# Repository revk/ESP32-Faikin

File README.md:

### Name change

Yes, it seems Daikin don't like Faikin, and I don't have the time or money to argue.

# ESP32-Faikout

Everyone knows Daikin make some of the best air conditioners out there, mechanically speaking. Sadly their WiFi control modules are not so good, especially the latest models which are all cloud based, require an internet connection to even work, and are slow.

This code/module provides local control via web interface, MQTT, and HomeAssistant integration, all with no cloud crap.

* There is also a new [Faikout Remote Control](https://remote.revk.uk/) available, BLE linked to the Faikout, with environmental sensors, available on Tindie now.

PCB designs are included, and also available to buy on [Tindie](https://www.tindie.com/stores/revk/), and on [Amazon UK](https://www.amazon.co.uk/dp/B0G1TP8XCQ). There are other people making and selling, e.g. on [eBay Australia](https://www.ebay.com.au/itm/186860658654).

I'd like to thank the contributors, but contributions are made and accepted on basis that you issue your contribution under the same GPL licence as the project. Forks are allowed on the basis that your forks are on the same GPL licence as the project.

## Trademark

This is an open source project, but bear in mind you cannot sell boards bearing the Andrews & Arnold Ltd name, the A&A logo, the registered trademark AJK logo, or the GS1 allocated EANs assigned to Andrews & Arnold Ltd.

## Further manuals / links

- [Work in progress / release notes](https://github.com/revk/ESP32-Faikout/wiki/Work-in-progress)
- [Wiring](https://github.com/revk/ESP32-Faikout/wiki/Wiring)
- [Setup](Manuals/Setup.md) Manual
- [Controls](Manuals/Controls.md) Manual
- [Advanced](Manuals/Advanced.md) Manual
- [ESP8266 port](https://github.com/Sonic-Amiga/ESP8266-Faikin) of this code
- [list of supported air-con](https://github.com/revk/ESP32-Faikout/wiki/List-of-confirmed-working-air-con-units) WiKi (please update as needed)
- [DoC](Manuals/DoC.md) and Vulnerability disclosure policy
- [S21](Manuals/S21.md) reverse engineered details of `S21` protocol

For support, see issues and discussions.

## PCB and case

The boards from [Tindie](https://www.tindie.com/stores/revk/), [eBay](https://www.ebay.com.au/itm/186860658654), and [Amazon UK](https://www.amazon.co.uk/dp/B0G1TP8XCQ) works with Daikin modules via an `S21` connector, or `X50A` and `X35A` connectors, or similar. The design is updated from time to time so may not look exactly like this.

The case design matches the PCB (check dates match). Designed for resin printing.

Supplied in a 70x70 panel as an assembled PCB with snap off parts down to two sizes. 45x36mm or 40x16mm.

## Why I made this

The history is that, after years of using Daikin air-con in my old home, and using the local http control, in my new house in Wales the WiFi was all cloud based with no local control, and useless, and slow. Just configuring it was a nightmare. I spent all day reverse engineering it and making a new module to provide local control. Pull requests and feature ideas welcome.

This whole project is almost entirely by me, but with some valuable contributions from others (thank you). All of my bits are copyright by me and Andrews & Arnold Ltd who sponsor the whole project, and released under GPL. Whilst not required by the licence, attribution and links would be appreciated if you reuse this.

## How to get one

As mentioned, [Tindie](https://www.tindie.com/stores/revk/), [eBay](https://www.ebay.com.au/itm/186860658654), and [Amazon UK](https://www.amazon.co.uk/dp/B0G1TP8XCQ).

But also, the PCB designs are published, including production files for [JLCPCB](https://jlcpcb.com). You need to remove trademarks, etc, and you would also need something to program them (TC2030 lead). Obviously you need some experience with PCB ordering and diagnostics if getting your own boards made.

# Set-up

Appears as access point with simple web page to set up on local WiFI. On iPhone the setup page auto-loads.

# Operation

Local interactive web control page using *hostname*.local, no app required, no external internet required.

- [Setup](Manuals/Setup.md) Manual
- [Controls](Manuals/Controls.md) Manual
- [Advanced](Manuals/Advanced.md) Manual

# Design

* KiCad PCB designs included, with JLCPCB production files
* 3D printed case STL files
* Documentation of reverse engineered protocol included

Basically, Daikin have gone all cloudy with the latest WiFi controllers. This module is designed to provide an alternative.

* Simple local web based control with live websocket status, easy to save as desktop icon on a mobile phone
* MQTT reporting and controls
* Works with Home Assistant over MQTT - note Home Assistant can work with HomeKit
* Includes linux mysql/mariadb based logging and graphing tools
* Works with [EnvMon](https://github.com/revk/ESP32-EnvMon) Environmental Monitor for finer control and status display
* or, works with BlueCoinT and Telink [BLE temperature sensor](Manuals/BLE.md) as a remote reference in an auto mode
* Automatically works out if S21 or X50 protocol (used on bigger/ducted units)
* Backwards compatible direct `/aircon/...` URLs

# Building code yourself

Git clone this `--recursive` to get all the submodules, and it should build with just `make`. There are make targets for other variations, but this hardware is the `make pico` or `make s3` version. The `make` actually runs the normal `idf.py` to build which then uses cmake. `make menuconfig` can be used to fine tune the settings, but the defaults should be mostly sane. `make flash` should work to program. If flashing yourself, you will need a programming lead, e.g. [Tazmotizer](https://github.com/revk/Shelly-Tasmotizer-PCB) or similar, and of course the full ESP IDF environment. The latest boards also have 4 pads for direct USB connection to flash with no adaptor. The modules on Amazon come pre-loaded and can upgrade over the air.

The code is normally set up to automatically upgrade the software, checking roughtly once a week. You can change this in settings via MQTT.

If you build yourself, you either need no code signing, or your own signing key. This will break auto-updates which try to load my code releases, so you need to adjuist settings `otahost` and `otaauto` accordingly. You can set these in the build config, along with WiFi settings, etc.

If you want to purchase a pre-loaded assembled PCB, see [Tindie](https://www.tindie.com/stores/revk/), and [Amazon UK](https://www.amazon.co.uk/dp/B0C2ZYXNYQ).

## Flashing code

You will need to connect a suitable programming lead. Boards have a header for USB. The very latest design (expected on Amazon around Sep 2024) has a tag-connect compatible header for a [TC2030-USB-NL](https://www.tag-connect.com/product/tc2030-usb-nl) lead. Note that the latest boards have testr pads on the back which include USB, so you can solder a USB lead if necessary.

See [https://github.com/revk/ESP32-RevK](https://github.com/revk/ESP32-RevK) for more details of how to flash the files easily.

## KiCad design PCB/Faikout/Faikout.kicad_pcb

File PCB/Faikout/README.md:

# Faikout

## Trademark

This is an open source project, but bear in mind you cannot sell boards or cases bearing the Andrews & Arnold Ltd name, the A&A logo, the registered trademark AJK logo, or the GS1 allocated EANs assigned to Andrews & Arnold Ltd.

## PCB Designs

These files are for use with [KiCAD](https://www.kicad.org).

- [Faikout](Faikout.kicad_pro)

## 3D

3D case designs are normally automatically created from the PCB so as to ensure correct details and placement of apertures, etc.

|Design|Bottom|Top|Combined|
|------|------|---|--------|
|Faikout||||

## PCB Images

---

*Auto generated README.md 2025-11-12T08:11:45*

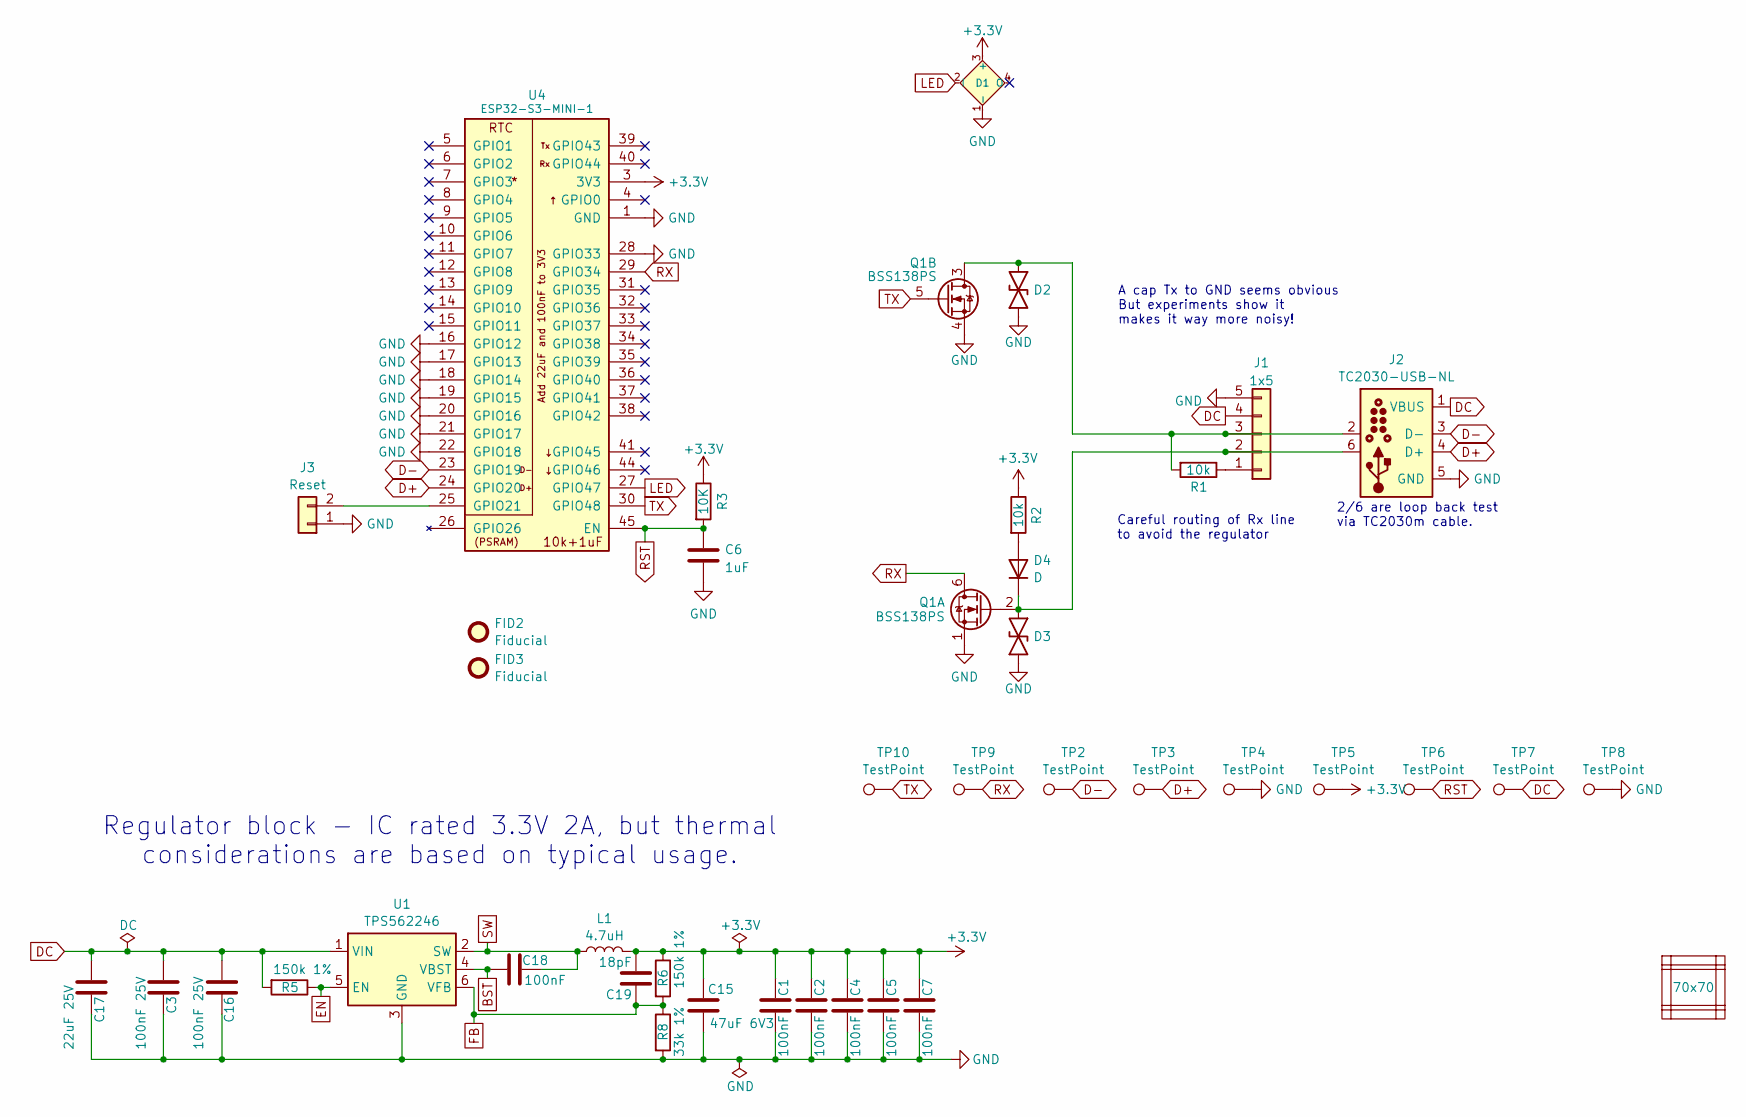
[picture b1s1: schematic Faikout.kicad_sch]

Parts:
C1, C2, C4, C5, C7, C18: 100nF; C_0201; MPN C76934
C3, C16: 100nF 25V; C_0402; MPN C56392
C6: 1uF; C_0201
C15: 47uF 6V3; C_0805; MPN C16780
C17: 22uF 25V; C_0805; MPN C45783
C19: 18pF; C_0201; MPN C62164
D1: XL-1615RGBC-2812B; SMD1615; MPN C5349954
D2, D3: DFN1006-2L; MPN C5137770
D4: D; D_0402; MPN C28642302
FID2, FID3: Fiducial; Fiducial_1mm_Mask2mm
J1: 1x5; JST_EH_S5B-EH_1x05_P2.50mm_Horizontal; MPN C265103
J2: TC2030-USB-NL; Tag-Connect_TC2030-IDC-NL_2x03_P1.27mm_Vertical
J3: Reset; AA-Pad
L1: 4.7uH; L_5x5; MPN C307876
PCB1: 70x70; PCB7070
Q1: BSS138PS; SOT-363_SC-70-6; MPN C193381
R1, R2: 10k; R_0201; MPN C106225
R3: 10K; R_0201; MPN C106225
R5, R6: 150k 1%; R_0201; MPN C310173
R8: 33k 1%; R_0201; MPN C320835
TP2, TP3, TP4, TP5, TP6, TP7, TP8, TP9, TP10: TestPoint; PAD-2mm
U1: TPS562246; SOT-563; MPN C41833479
U4: ESP32-S3-MINI-1; MPN C3013941
V1, V2, V3, V4, V5, V6: VCUT70N

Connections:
+3.3V: C1.2, C2.2, C4.2, C5.2, C7.2, C15.1, C19.2, D1.3 (+), L1.2, R2.1, R3.1, R6.1, TP5.1, U4.3 (3V3)
BST: C18.1, U1.4 (VBST)
D+: J2.4 (D+), TP3.1, U4.24 (GPIO20)
D-: J2.3 (D-), TP2.1, U4.23 (GPIO19)
DC: C3.1, C16.1, C17.1, J1.4, J2.1 (VBUS), R5.2, TP7.1, U1.1 (VIN)
EN: R5.1, U1.5 (EN)
FB: C19.1, R6.2, R8.1, U1.6 (VFB)
GND: C1.1, C2.1, C3.2, C4.1, C5.1, C6.2, C7.1, C15.2, C16.2, C17.2, D1.1 (-), D2.1, D3.1, J1.5, J2.5 (GND), J3.1, Q1.1 (SN), Q1.4 (DP), R8.2, TP4.1, TP8.1, U1.3 (GND), U4.1 (GND), U4.2 (GND), U4.16 (GPIO12), U4.17 (GPIO13), U4.18 (GPIO14), U4.19 (GPIO15), U4.20 (GPIO16), U4.21 (GPIO17), U4.22 (GPIO18), U4.28 (GPIO33), U4.42 (GND), U4.43 (GND), U4.46 (GND), U4.47 (GND), U4.48 (GND), U4.49 (GND), U4.50 (GND), U4.51 (GND), U4.52 (GND), U4.53 (GND), U4.54 (GND), U4.55 (GND), U4.56 (GND), U4.57 (GND), U4.58 (GND), U4.59 (GND), U4.60 (GND), U4.61 (GND), U4.62 (GND), U4.63 (GND), U4.64 (GND), U4.65 (GND)
LED: D1.2 (I), U4.27 (GPIO47)
unnamed: D4.2 (A), R2.2
unnamed: D3.2, D4.1 (K), J1.2, J2.6, Q1.2 (GN)
unnamed: J1.1, R1.1
unnamed: D2.2, J1.3, J2.2, Q1.3 (SP), R1.2
unnamed: J3.2, U4.25 (GPIO21)
RST: C6.1, R3.2, TP6.1, U4.45 (EN)
RX: Q1.6 (DN), TP9.1, U4.29 (GPIO34)
SW: C18.2, L1.1, U1.2 (SW)
TX: Q1.5 (GP), TP10.1, U4.30 (GPIO48)

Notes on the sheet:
Careful routing of Rx line to avoid the regulator
2/6 are loop back test via TC2030m cable.
A cap Tx to GND seems obvious But experiments show it makes it way more noisy!
Regulator block - IC rated 3.3V 2A, but thermal considerations are based on typical usage.

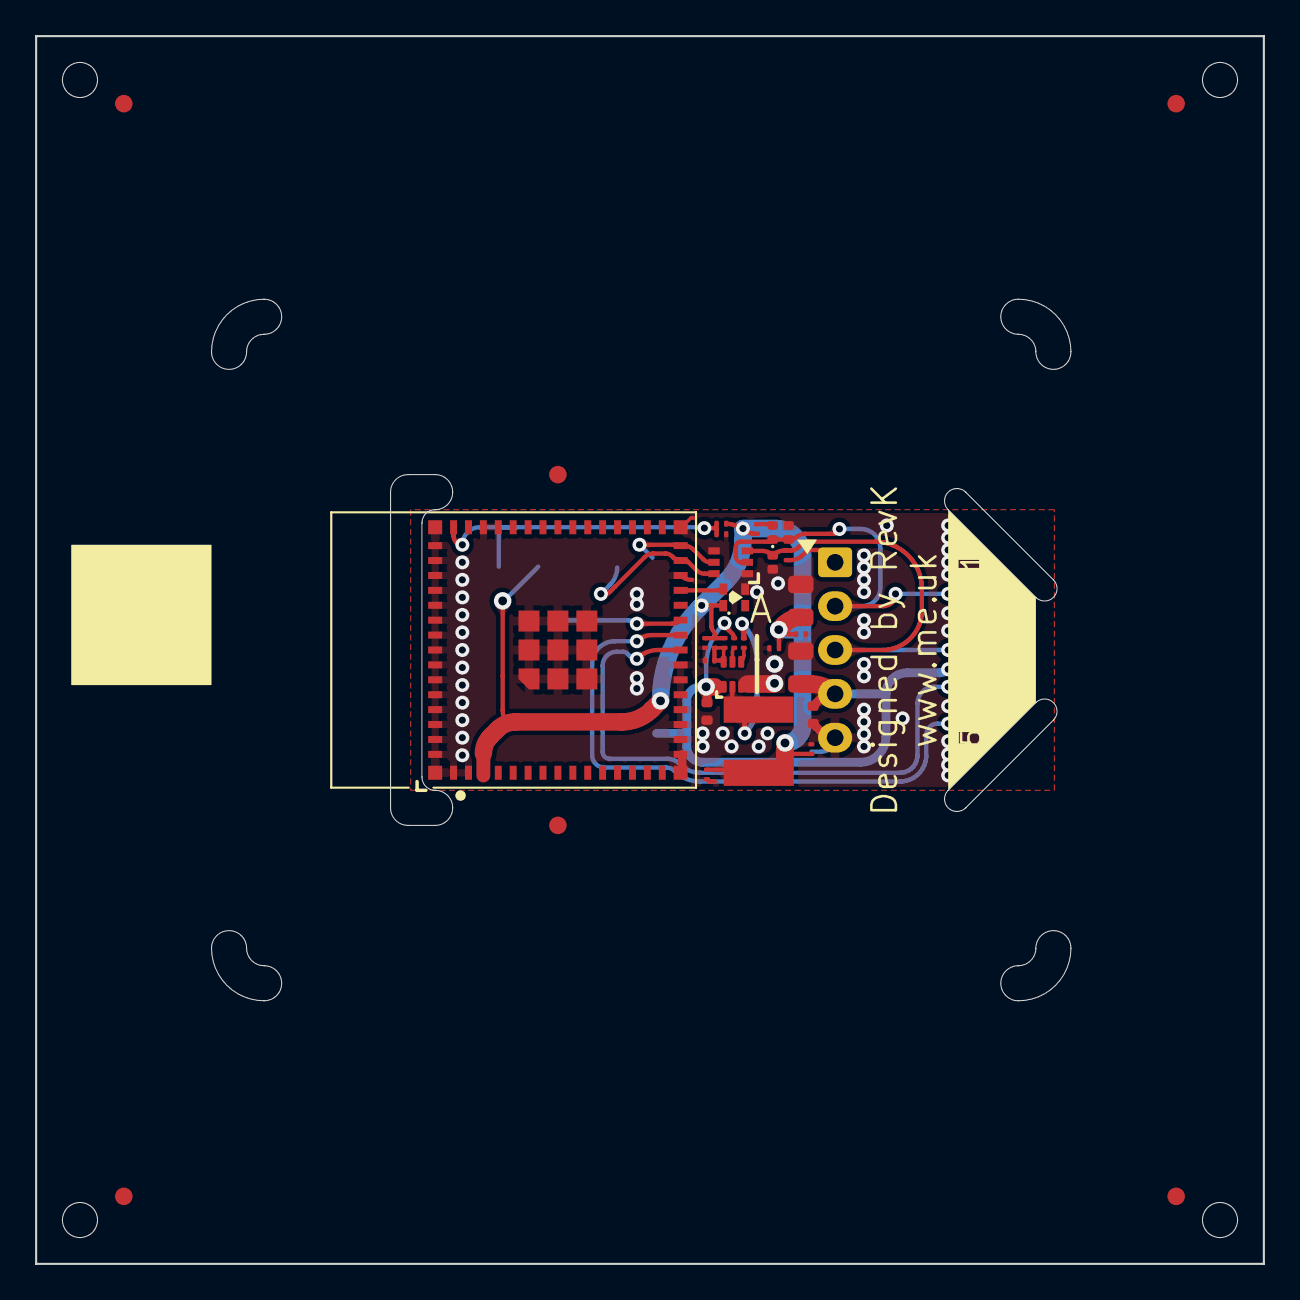
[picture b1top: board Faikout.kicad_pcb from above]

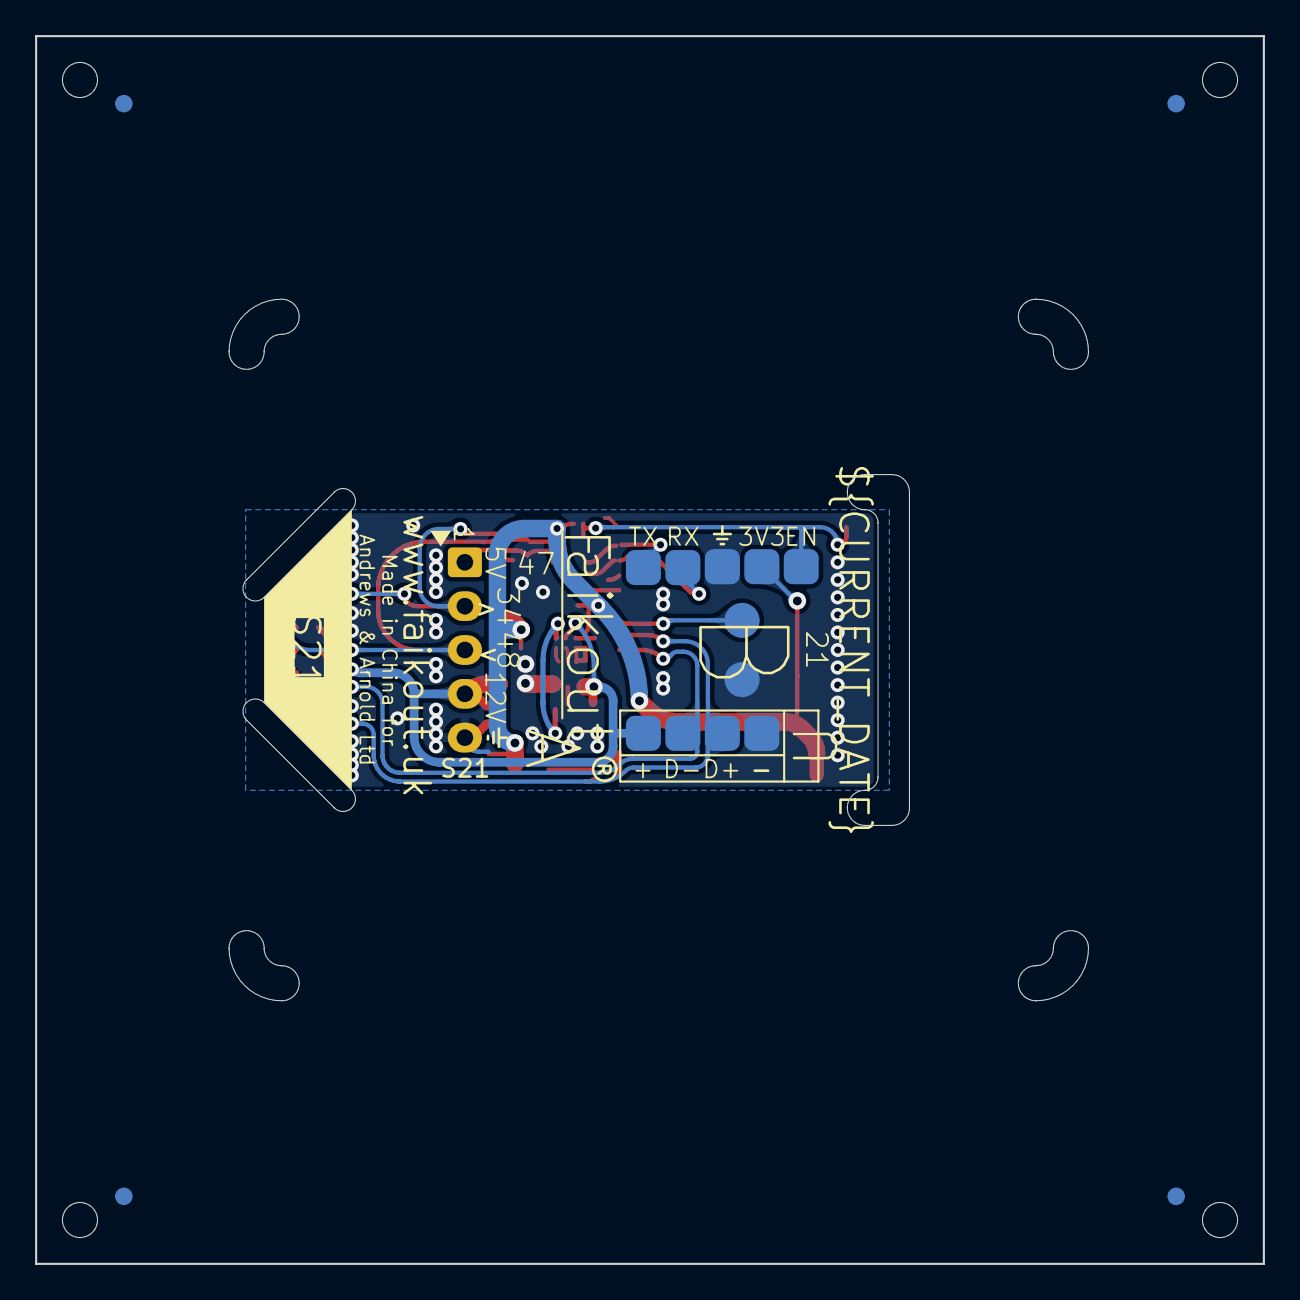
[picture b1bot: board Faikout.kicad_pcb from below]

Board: 2 copper layers, 70.0 x 70.0 mm, 47 parts (12 on the bottom side), 18 nets.

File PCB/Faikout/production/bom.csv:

Designator,Footprint,Quantity,Value,LCSC Part #
"C1, C18, C2, C4, C5, C7",C_0201,6,100nF,C76934
C15,C_0805,1,47uF 6V3,C16780
"C16, C3",C_0402,2,100nF 25V,C56392
C17,C_0805,1,22uF 25V,C45783
C19,C_0201,1,18pF,C62164
C6,C_0201,1,1uF,
D1,SMD1615-Blind,1,XL-1615RGBC-2812B,C5349954
"D2, D3",DFN1006-2L,2,~,C5137770
D4,D_0402,1,D,C28642302
J1,JST_EH_S5B-EH_1x05_P2.50mm_Horizontal,1,1x5,C265103
L1,L_5x5,1,4.7uH,C307876
Q1,SOT-363_SC-70-6,1,BSS138PS,C193381
"R1, R2, R3",R_0201,3,10k,C106225
"R5, R6",R_0201,2,150k 1%,C310173
R8,R_0201,1,33k 1%,C320835
U1,SOT-563,1,TPS562246,C41833479
U4,ESP32-S3-MINI-1,1,ESP32-S3-MINI-1-N4R2,C3013941

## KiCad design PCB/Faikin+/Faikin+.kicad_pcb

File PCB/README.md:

# PCB designs

The design is in [KiCad](https://www.kicad.org) and has production files for JLCPCB. The boards are available on [Amazon](https://www.amazon.co.uk/dp/B0C2ZYXNYQ).

The `PCBCase` directory is a tool for making 3D cases from the PCBs files, these are usually kept up to date as an `.stl` file in the `Faikout` directory. The `Makefile` simply runs this tool.

## Trademark

This is an open source project, but bear in mind you cannot sell boards bearing the Andrews & Arnold Ltd name, the A&A logo, the registered trademark AJK logo, or the GS1 allocated EANs assigned to Andrews & Arnold Ltd.

## Panel

Supplied in a 70x70 panel as an assembled PCB with snap off parts down to two sizes. 45x36mm or 40x16mm.

The panel includes slots and v-cuts to allow the unwanted parts of the panel to be snapped off. On the thicker (1.6mm) boards this can be a tad un-nerving, but just bend along the v-cut to snap the board on the cut line. I make the boards at 1.2mm thickness to make this easier.

The board design also allows the panel to be snapped off down to a 45mm x 36mm small board. This is the same size as commonly used for built-in Daikin WiFi modules, so if replacing the standard Daikin WiFi, it should fit exactly in the case. Obviously this only applies to some models.

You can further snap off down to the actual module, which is currently 40mm x 16mm. This is the usual way the module is used. The 3D print design is for this board.

The back of the board has no components, making it simple to stick to a flat surface with tape - you may want to crop the pins on the 5 pin connector if doing this. Do not stick to a metal surface as this may impact the WiFi or short the pins.

## S21 Connector

The connector is `JST-EH` 5 pin connector. This seems to be pretty standard in Daikin units. It is the connector used on the Daikin WiFi modules `BRP069B41` and `BRP069C41`. This means it should usually be possible to get a lead for your Daikin to a `JST-EH` 5 pin `S21` connector. If you have an `S21` connector on your air-con it will likely be the same pin out, so one to one wiring. If you have an `X50A` connector the wiring is different, and getting a suitable lead is a good idea.

From what we can tell, the `S21` pin out is as follows :-

|Pin|Meaning|
|---|-------|
|1|5V (not always present)|
|2|Tx from aircon - 5V logic levels|
|3|Rx to aircon - expects 5V logic and has 5V pull up, but some modeles work at 3.3V|
|4|12V, or 14V. We accept 4V to 36V|
|5|GND|

However, there are jumper wires readily available that can be used easily with these connectors, and can be used to connect to the `S21` connector on the aircon PCB one wire at a time.

**Please take care with your air-con unit - disconnect power before opening, and anything you do is at your own risk.**

## GPIO

This board is designed to work with the Daikin air-con, but it is a general purpose board. The latest boards use `ESP32-S3-MINI-N4R2` processor, with previous being `ESP32-MINI-PICO-01`.

The current boards include the GPIO numbers clearly in inverse silk screen.

For example, on this image, GPIO `34` and `48` for Tx and Rx. GPIO `47` is for the WS2812 style LED. GPIO `21` is one of two round pads.

The two round pads in the A&A logo can be shorted three times in a row to factory reset.

There are also test pins which allow connection for USB, and for diagnostics during production. A TC2030 connector is used for production programming.

## Programming

The board has pads for a TC2030 USB lead for programming directly using `esptool`.

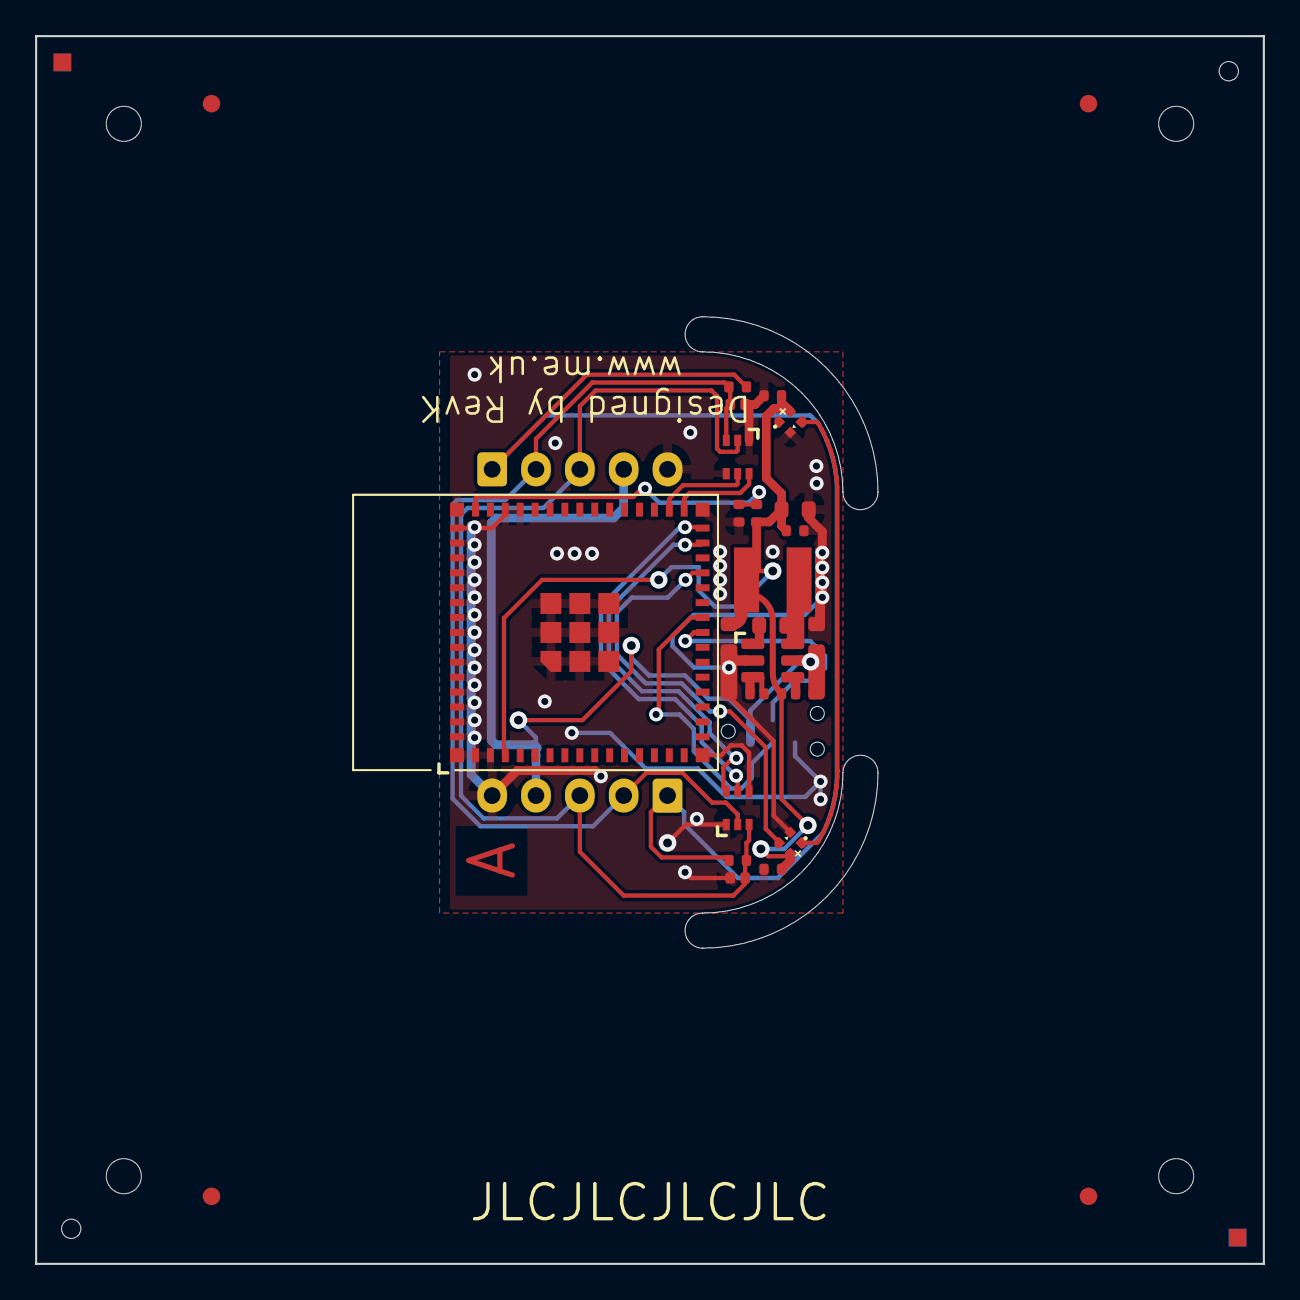
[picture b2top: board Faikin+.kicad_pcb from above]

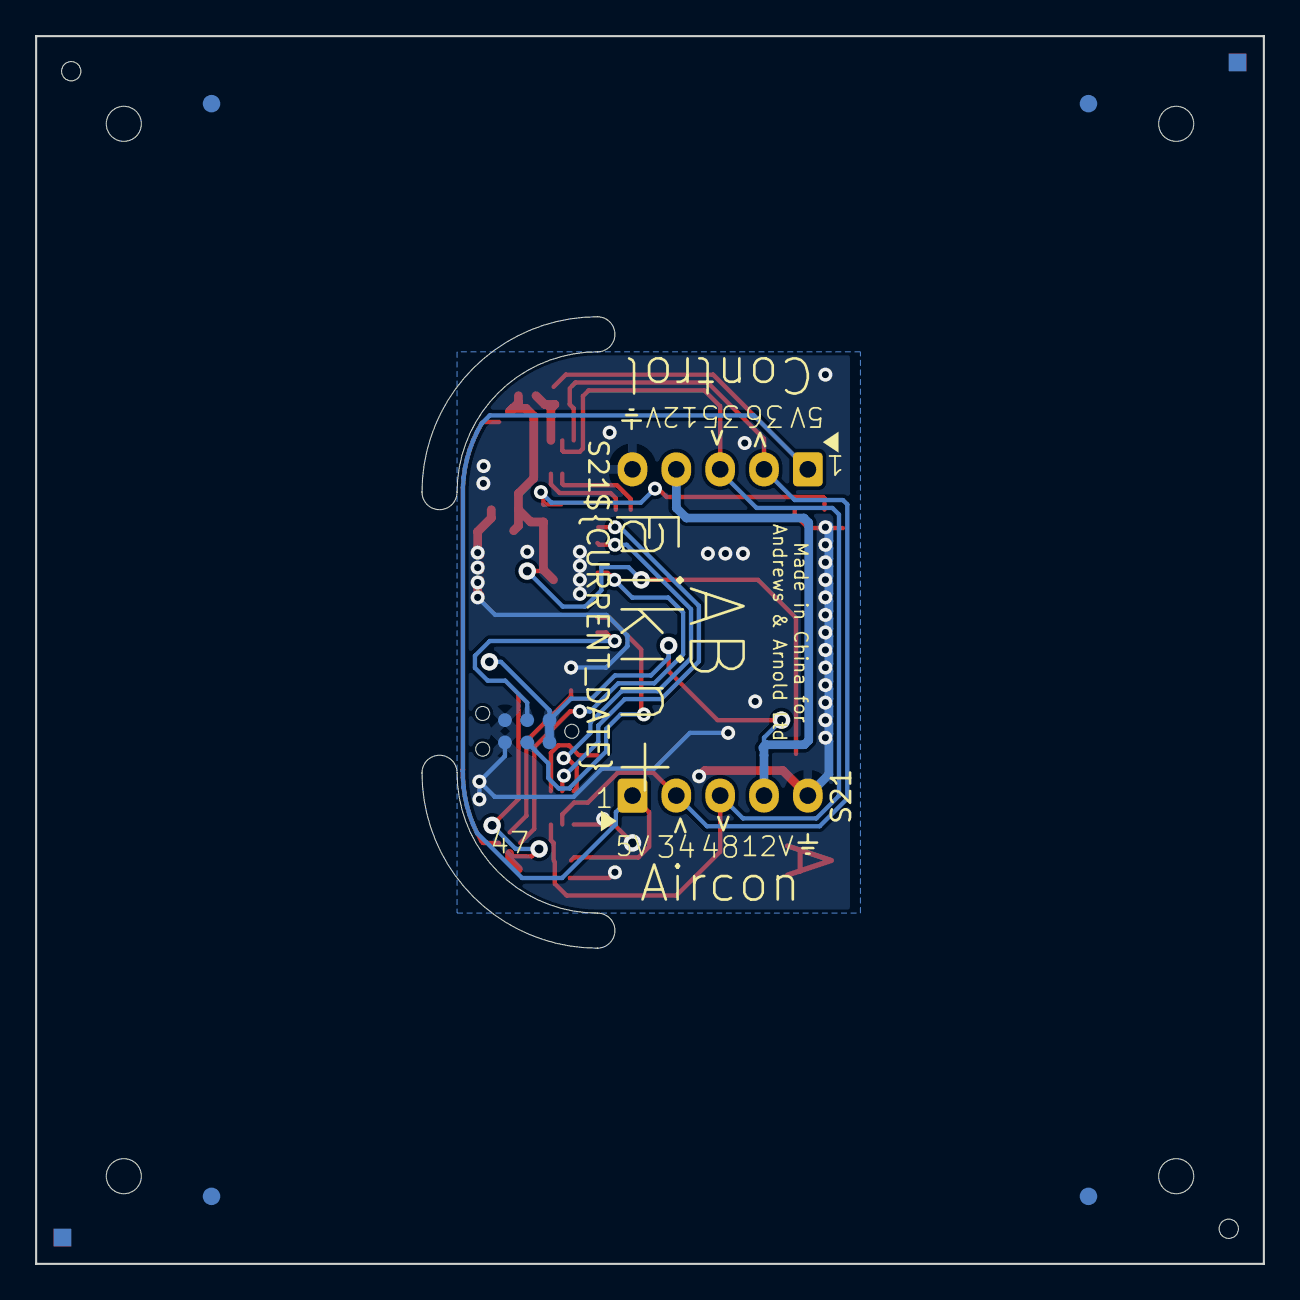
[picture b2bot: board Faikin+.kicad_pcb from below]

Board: 2 copper layers, 70.0 x 70.0 mm, 31 parts (2 on the bottom side), 15 nets.

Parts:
C1, C2, C3: 100nF; C_0402
C5: 22uF; C_0603
C6: 1uF; C_0402
C8: 10uF 35V; C_0603_
C9: 10uF 6.3V; C_0603_
C10: 100nF; C_0603_
D1, D4: XL-1010RGBC-WS2812B; SMD1010
D2, D3: DFN1006-2L
J1, J4: 1x5; JST_EH_S5B-EH_1x05_P2.50mm_Horizontal
J5: TC2030-USB-NL-DS; Tag-Connect_TC2030-IDC-NL_2x03_P1.27mm_Vertical
L2: 10uH; L_4x4_
PCB1: 70x70; PCB7070
Q1, Q2: BSS138PS; SOT-363_SC-70-6
R1, R2: 10k; R_0402
R3: 10K; R_0402
R9: 124k; R_0402_
R10: 39k2; R_0402_
R11: 1M; R_0402_
U3: MD8942; SOT-23-6-MD8942
U4: ESP32-S3-MINI-1
V1, V2, V5, V6: VCUT70N

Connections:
+3.3V: C1.1, C2.1, C3.1, C5.1, D1.2 (+), D4.2 (+), R3.1, U3.8 (VOUT), U4.3 (3V3)
D+: J5.4 (D+), U4.24 (GPIO20)
D-: J5.3 (D-), U4.23 (GPIO19)
DC: J1.4, J4.4, J5.1 (VBUS), J5.2 (VBUS), U3.5 (VIN)
GND: C1.2, C2.2, C3.2, C5.2, C6.2, D1.3 (-), D2.1, D3.1, D4.3 (-), J1.5, J4.5, J5.5 (GND), J5.6 (GND), Q1.1 (SN), Q1.4 (DP), Q2.1 (SN), Q2.4 (DP), U3.2 (GND), U3.7 (GND), U4.1 (GND), U4.2 (GND), U4.42 (GND), U4.43 (GND), U4.46 (GND), U4.47 (GND), U4.48 (GND), U4.49 (GND), U4.50 (GND), U4.51 (GND), U4.52 (GND), U4.53 (GND), U4.54 (GND), U4.55 (GND), U4.56 (GND), U4.57 (GND), U4.58 (GND), U4.59 (GND), U4.60 (GND), U4.61 (GND), U4.62 (GND), U4.63 (GND), U4.64 (GND), U4.65 (GND)
LED: D1.4 (I), U4.27 (GPIO47)
unnamed: D1.1 (O), D4.4 (I)
unnamed: J1.1, J4.1, R1.1, R2.2
unnamed: C6.1, R3.2, U4.45 (EN)
RX: Q1.6 (DN), U4.29 (GPIO34)
RX2: Q2.6 (DN), U4.31 (GPIO35)
S21RX: D3.2, J1.2, J4.2, Q1.2 (GN), Q2.3 (SP), R2.1
S21TX: D2.2, J1.3, J4.3, Q1.3 (SP), Q2.2 (GN), R1.2
TX: Q1.5 (GP), U4.30 (GPIO48)
TX2: Q2.5 (GP), U4.32 (GPIO36)

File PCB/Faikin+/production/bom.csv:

Designator,Footprint,Quantity,Value,LCSC Part #
"C1, C2, C3",C_0402,3,100nF,
C10,C_0603_,1,100nF,
C5,C_0603,1,22uF,
C6,C_0402,1,1uF,
C8,C_0603_,1,10uF 35V,C194427
C9,C_0603_,1,10uF 6.3V,C1691
"D1, D4",SMD1010,2,XL-1010RGBC-WS2812B,C5349953
"D2, D3",DFN1006-2L,2,~,C5137770
"J1, J4",JST_EH_S5B-EH_1x05_P2.50mm_Horizontal,2,1x5,C265103
L2,L_4x4_,1,10uH,
"Q1, Q2",SOT-363_SC-70-6,2,BSS138PS,C193381
"R1, R2, R3",R_0402,3,10k,
R10,R_0402_,1,39k2,
R11,R_0402_,1,1M,
R9,R_0402_,1,124k,C138062
U3,SOT-23-6-MD8942,1,MD8942,C2684786
U4,ESP32-S3-MINI-1,1,ESP32-S3-MINI-1,C3013941

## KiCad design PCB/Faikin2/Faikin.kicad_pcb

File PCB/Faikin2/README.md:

# PCB

These files are for use in [KiCad](https://www.kicad.org) so can be edited as needed.

You should, technically, remove the A&A and AJK logos as they are trademark. If you are using for yourself, then fine, but you must not trade (i.e. sell boards you make) with these logos.

## Ordering

There are also `production` files for [JLCPCB](https://jlcpcb.com)

When ordering, you need the `gerber.zip`, `bom.csv`, and `position.csv` files.

### PCB

- Order Number: Specify location

### Assembly

- PCBA Type: Standard
- Assembly Side: Top Side
- Tooling holes: Added by Customer

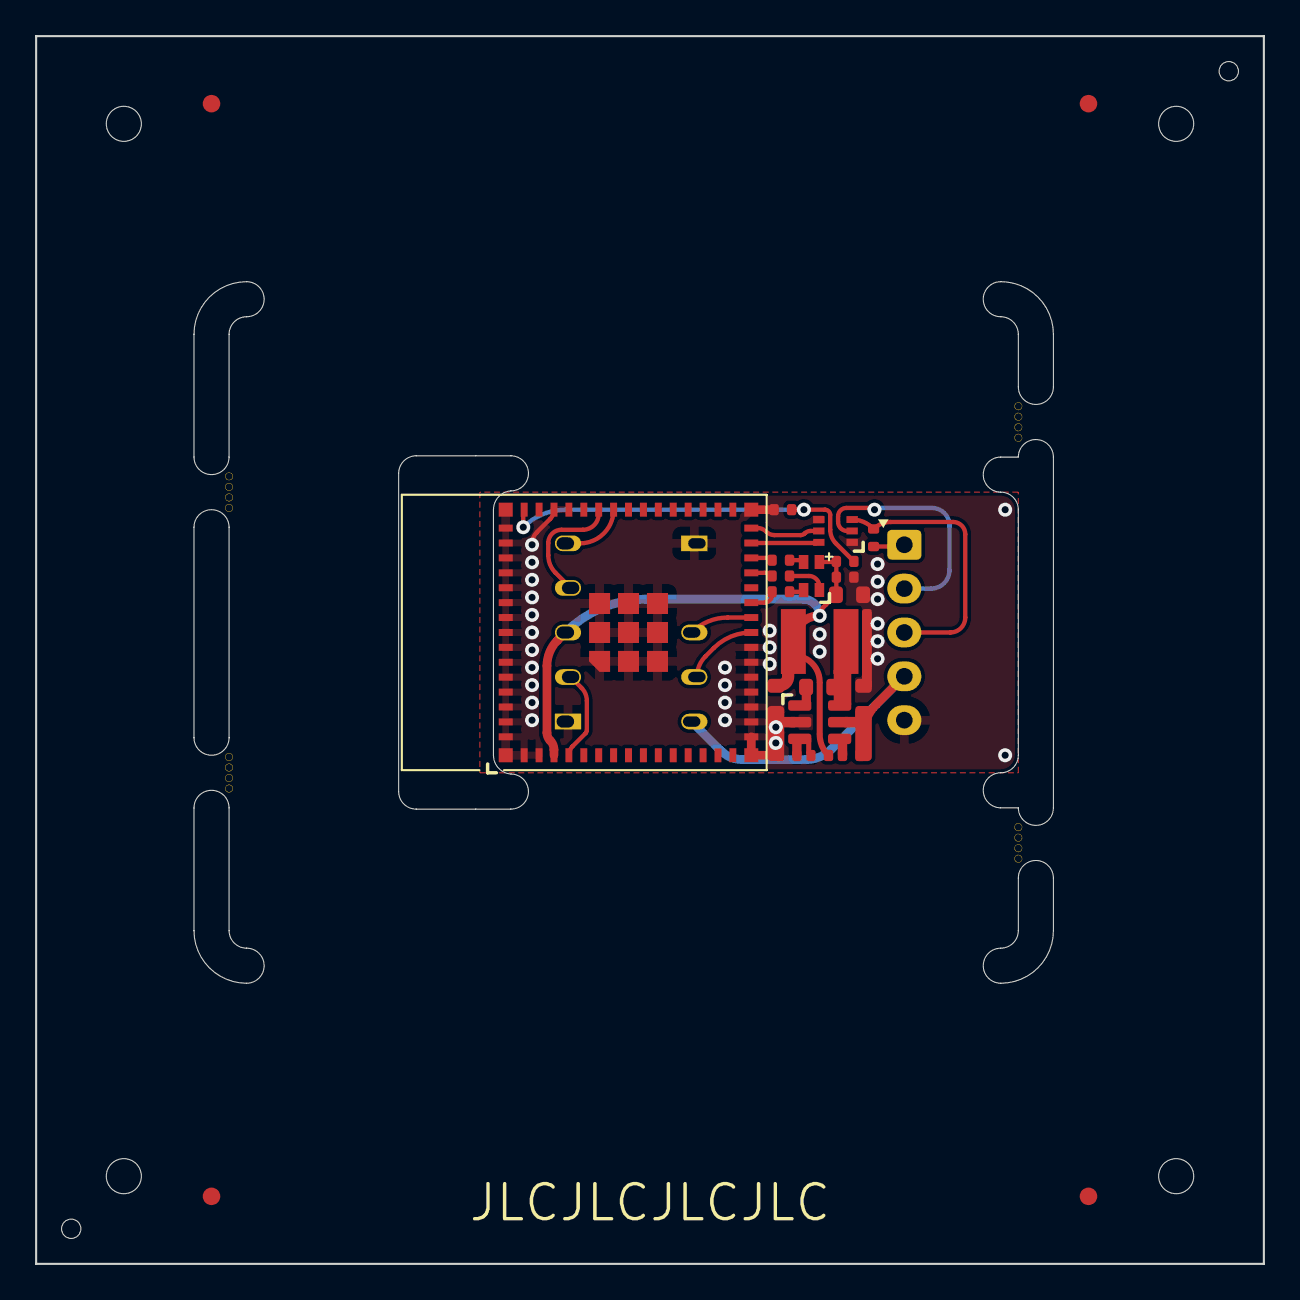
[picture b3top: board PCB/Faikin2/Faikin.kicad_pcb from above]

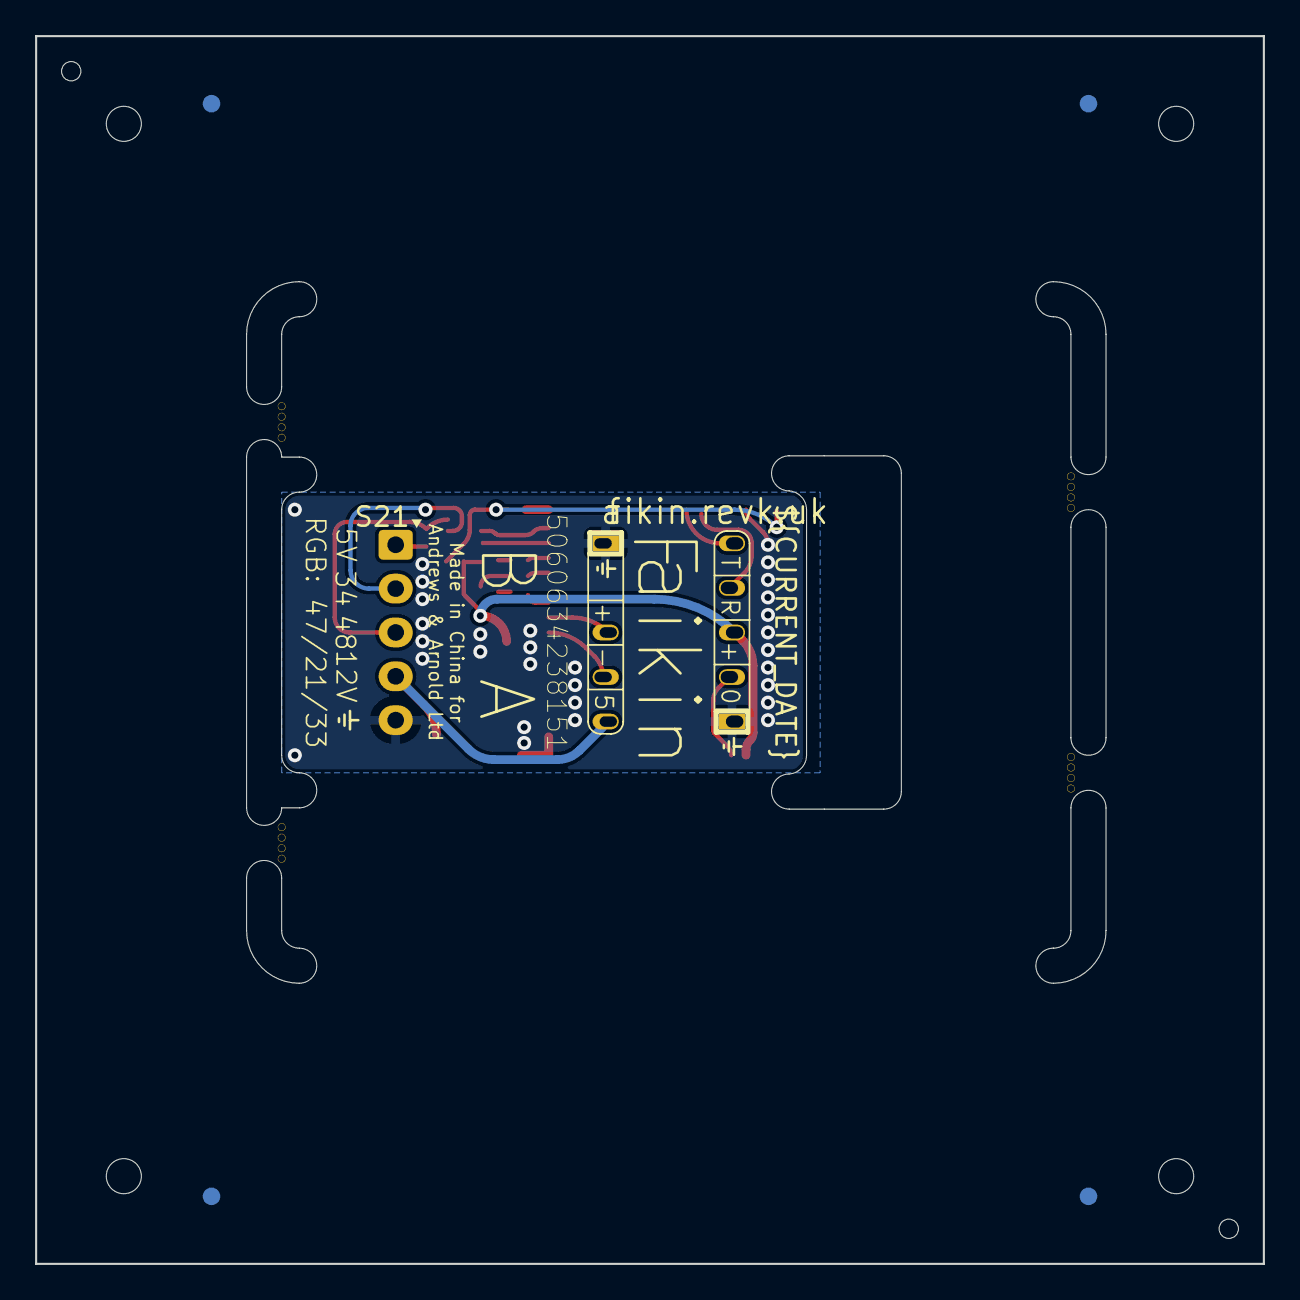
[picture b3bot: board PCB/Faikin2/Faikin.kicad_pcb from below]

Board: 2 copper layers, 70.0 x 70.0 mm, 31 parts (3 on the bottom side), 20 nets.

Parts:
C2: 100nF; C_0402
C5: 22uF; C_0603
C6: 1uF; C_0402
C8: 10uF 50V; C_0603_
C9: 10uF 6.3V; C_0603_
C10: 100nF; C_0603_
D2: RGB; LED-RGB-1.6x1.6
J1: 1x5; JST_EH_S5B-EH_1x05_P2.50mm_Horizontal
J2: Shelly
J3: USB-PROG
L2: 10uH; L_4x4_
PCB1: 70x70; PCB7070
Q1: BSS138PS; SOT-363_SC-70-6
R1: 10k; R_0402
R3: 10K; R_0402
R5: 680R; R_0402
R6: 2K; R_0402
R9: 124k; R_0402_
R10: 39k2; R_0402_
R11: 1M; R_0402_
R12: 220R; R_0402
U3: MD8942; SOT-23-6-MD8942
U4: ESP32-S3-MINI-1
V1, V2, V3, V4: VCUT70
Z1, Z2, Z3, Z4: Hidden; PCB-Join1

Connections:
+3.3V: C2.1, C5.1, D2.4 (A), J2.3 (3V3), R3.1, U3.8 (VOUT), U4.3 (3V3)
B: R12.2, U4.28 (GPIO33)
D+: J3.3 (D+), U4.24 (GPIO20)
D-: J3.2 (D-), U4.23 (GPIO19)
DC: J1.4, J3.1 (VBUS), U3.5 (VIN)
G: R6.2, U4.25 (GPIO21)
GND: C2.2, C5.2, C6.2, J1.5, J2.1 (GND), J3.4 (GND), Q1.1 (SN), Q1.4 (DP), U3.2 (GND), U3.7 (GND), U4.1 (GND), U4.2 (GND), U4.16 (GPIO12), U4.17 (GPIO13), U4.18 (GPIO14), U4.19 (GPIO15), U4.20 (GPIO16), U4.21 (GPIO17), U4.22 (GPIO18), U4.42 (GND), U4.43 (GND), U4.46 (GND), U4.47 (GND), U4.48 (GND), U4.49 (GND), U4.50 (GND), U4.51 (GND), U4.52 (GND), U4.53 (GND), U4.54 (GND), U4.55 (GND), U4.56 (GND), U4.57 (GND), U4.58 (GND), U4.59 (GND), U4.60 (GND), U4.61 (GND), U4.62 (GND), U4.63 (GND), U4.64 (GND), U4.65 (GND)
unnamed: D2.3 (BK), R12.1
unnamed: D2.2 (GK), R6.1
unnamed: D2.1 (RK), R5.1
unnamed: J1.1, R1.1
unnamed: J1.2, Q1.2 (GN)
unnamed: J1.3, Q1.3 (SP), R1.2
unnamed: J2.2 (0), U4.4 (GPIO0)
unnamed: J2.4 (Rx), U4.40 (GPIO44)
unnamed: J2.5 (Tx), U4.39 (GPIO43)
unnamed: C6.1, R3.2, U4.45 (EN)
R: R5.2, U4.27 (GPIO47)
RX: Q1.6 (DN), U4.29 (GPIO34)
TX: Q1.5 (GP), U4.30 (GPIO48)

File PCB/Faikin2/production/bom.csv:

Designator,Footprint,Quantity,Value,LCSC Part #
C10,C_0603_,1,100nF,
C2,C_0402,1,100nF,
C5,C_0603,1,22uF,
C6,C_0402,1,1uF,
C8,C_0603_,1,10uF 50V,C1591
C9,C_0603_,1,10uF 6.3V,C1691
D2,LED-RGB-1.6x1.6,1,RGB,C264508
J1,JST_EH_S5B-EH_1x05_P2.50mm_Horizontal,1,1x5,C265103
J3,USB-PROG,1,USB-PROG,
L2,L_4x4_,1,10uH,
Q1,SOT-363_SC-70-6,1,BSS138PS,C2912548
"R1, R3",R_0402,2,10k,
R10,R_0402_,1,39k2,
R11,R_0402_,1,1M,
R12,R_0402,1,220R,
R5,R_0402,1,680R,
R6,R_0402,1,2K,
R9,R_0402_,1,124k,
U3,SOT-23-6-MD8942,1,MD8942,C2684786
U4,ESP32-S3-MINI-1,1,ESP32-S3-MINI-1,C3013941
